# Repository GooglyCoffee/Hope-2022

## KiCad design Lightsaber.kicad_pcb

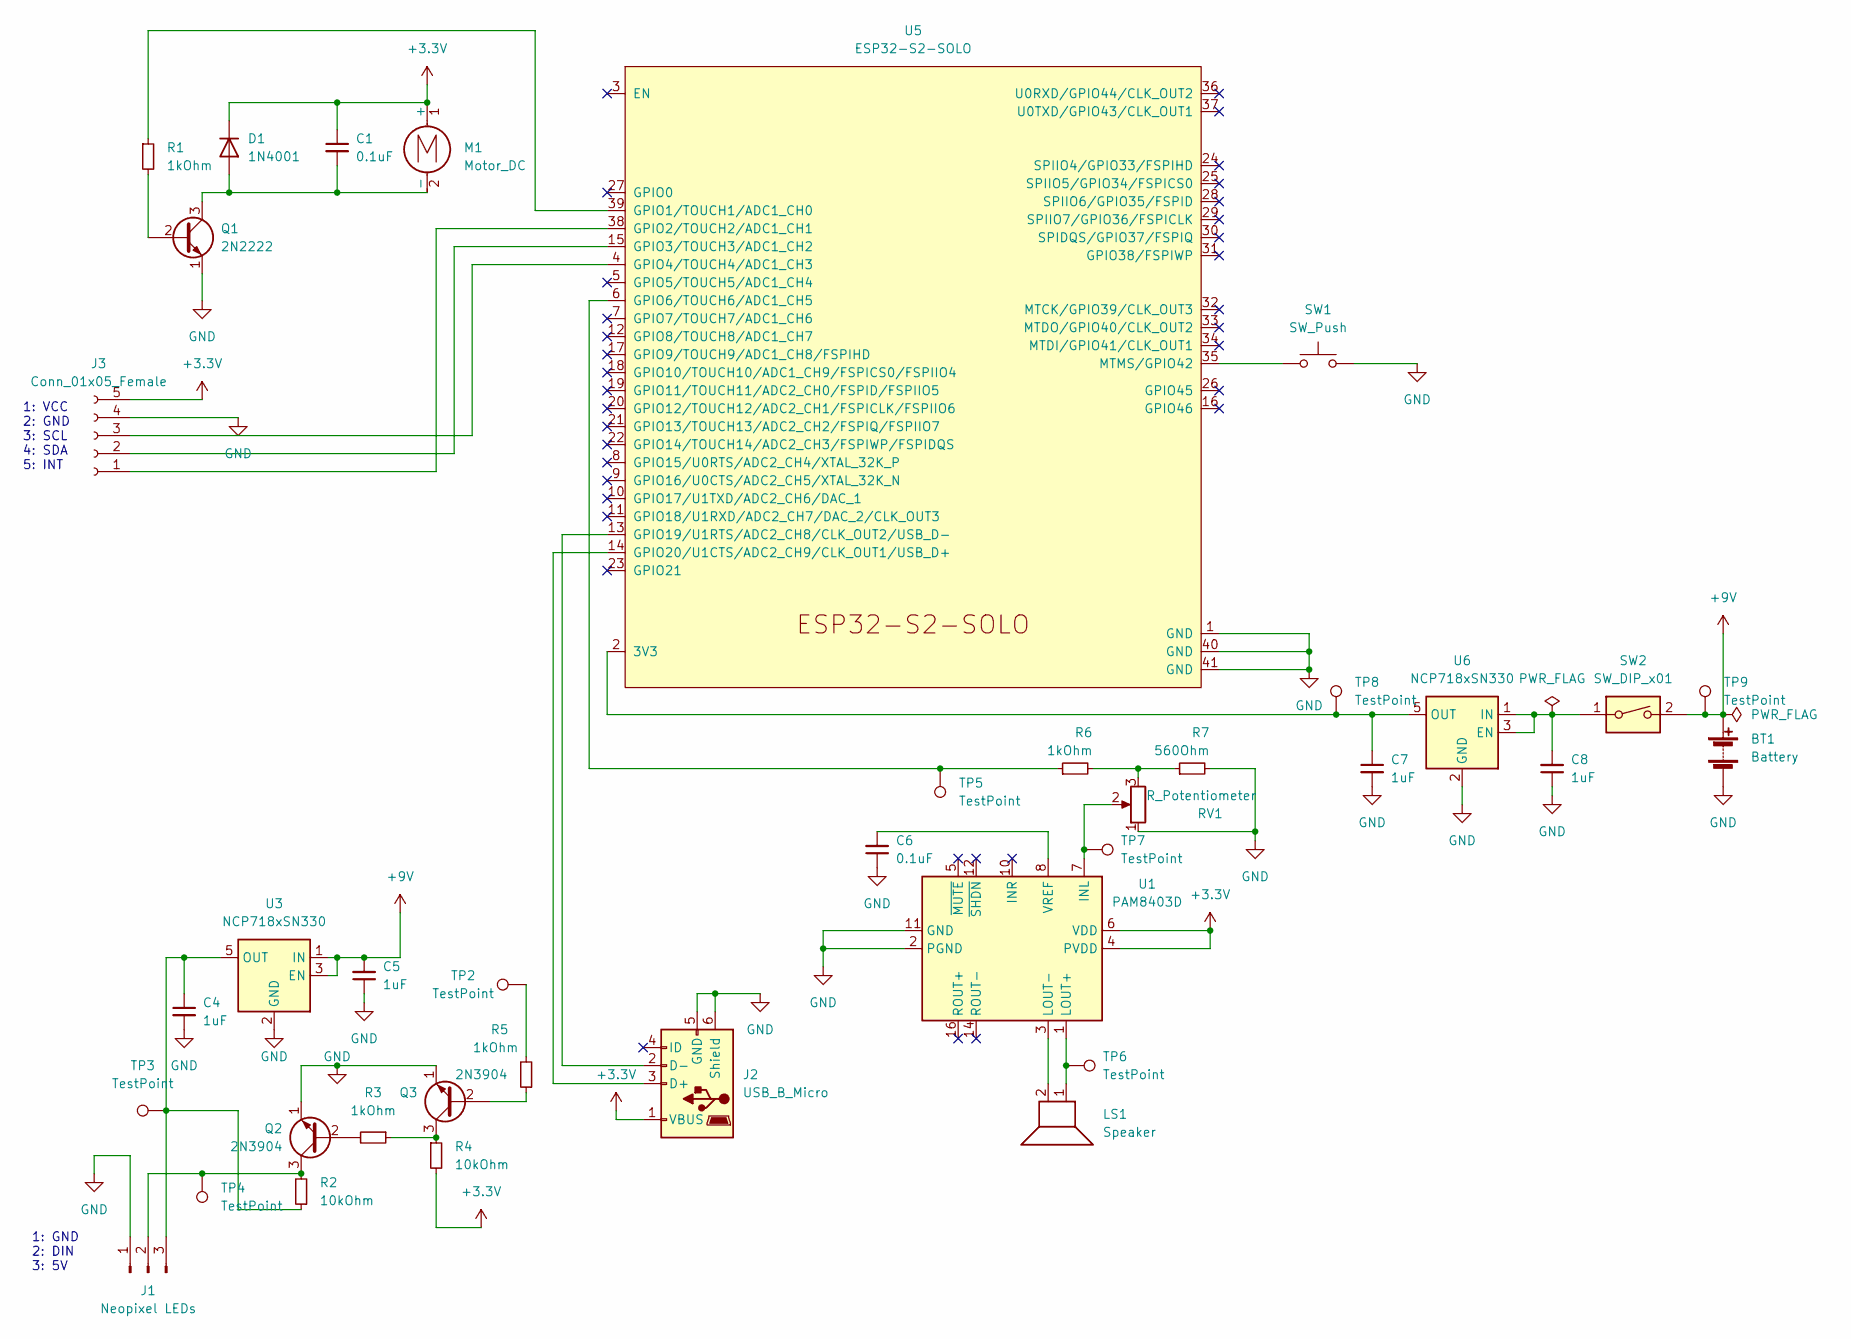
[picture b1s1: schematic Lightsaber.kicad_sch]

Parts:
BT1: Battery
C1, C6: 0.1uF; C_0201_0603Metric
C4, C5, C7, C8: 1uF; C_0603_1608Metric
D1: 1N4001; D_SOD-123F
J1: Neopixel LEDs; LED strip
J2: USB_B_Micro; USB_Micro-B_Molex-105017-0001
J3: Conn_01x05_Female; PinSocket_1x05_P2.54mm_Vertical
LS1: Speaker
M1: Motor_DC; Motor
Q1: 2N2222; TO-39-3
Q2, Q3: 2N3904; TO-92_Inline
R1, R3, R5, R6: 1kOhm; R_0603_1608Metric
R2, R4: 10kOhm; R_0603_1608Metric
R7: 560Ohm; R_0603_1608Metric
RV1: R_Potentiometer; Potentiometer
SW1: SW_Push; Switch
SW2: SW_DIP_x01; Switch toggle
TP2, TP3, TP4, TP5, TP6, TP7, TP8, TP9: TestPoint; PinHeader_1x01_P1.00mm_Vertical
U1: PAM8403D; SOP-16_3.9x9.9mm_P1.27mm
U3, U6: NCP718xSN330; SOT-23-5
U5: ESP32-S2-SOLO

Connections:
+3.3V: C1.1, D1.1 (K), J2.1 (VBUS), J3.5, M1.1 (+), R4.2, U1.4 (PVDD), U1.6 (VDD), U1.13 (PVDD)
+9V: BT1.1 (+), C5.2, SW2.2, TP9.1, U3.1 (IN), U3.3 (EN)
GND: BT1.2 (-), C4.2, C5.1, C6.1, C7.2, C8.1, J1.1, J2.5 (GND), J2.6 (Shield), J3.4, Q1.1 (E), Q2.1 (E), Q3.1 (E), R7.2, RV1.1, SW1.2, U1.2 (PGND), U1.11 (GND), U1.15 (PGND), U3.2 (GND), U5.1 (GND), U5.40 (GND), U5.41 (GND), U6.2 (GND)
unnamed: C1.2, D1.2 (A), M1.2 (-), Q1.3 (C)
unnamed: C4.1, J1.3, R2.1, TP3.1, U3.5 (OUT)
unnamed: C6.2, U1.8 (VREF)
unnamed: C7.1, TP8.1, U5.2 (3V3), U6.5 (OUT)
unnamed: C8.2, SW2.1, U6.1 (IN), U6.3 (EN)
unnamed: J1.2, Q2.3 (C), R2.2, TP4.1
unnamed: J2.2 (D-), U5.13 (GPIO19/U1RTS/ADC2_CH8/CLK_OUT2/USB_D-)
unnamed: J2.3 (D+), U5.14 (GPIO20/U1CTS/ADC2_CH9/CLK_OUT1/USB_D+)
unnamed: LS1.1, TP6.1, U1.1 (LOUT+)
unnamed: LS1.2, U1.3 (LOUT-)
unnamed: Q1.2 (B), R1.2
unnamed: Q2.2 (B), R3.2
unnamed: Q3.2 (B), R5.1
unnamed: Q3.3 (C), R3.1, R4.1
unnamed: R1.1, U5.39 (GPIO1/TOUCH1/ADC1_CH0)
unnamed: R5.2, TP2.1
unnamed: R6.1, TP5.1, U5.6 (GPIO6/TOUCH6/ADC1_CH5)
unnamed: R6.2, R7.1, RV1.3
unnamed: RV1.2, TP7.1, U1.7 (INL)
unnamed: SW1.1, U5.35 (MTMS/GPIO42)
unnamed: J3.3, U5.4 (GPIO4/TOUCH4/ADC1_CH3)
unnamed: J3.2, U5.15 (GPIO3/TOUCH3/ADC1_CH2)
unnamed: J3.1, U5.38 (GPIO2/TOUCH2/ADC1_CH1)

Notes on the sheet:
1: GND 2: DIN 3: 5V
1: VCC 2: GND 3: SCL 4: SDA 5: INT

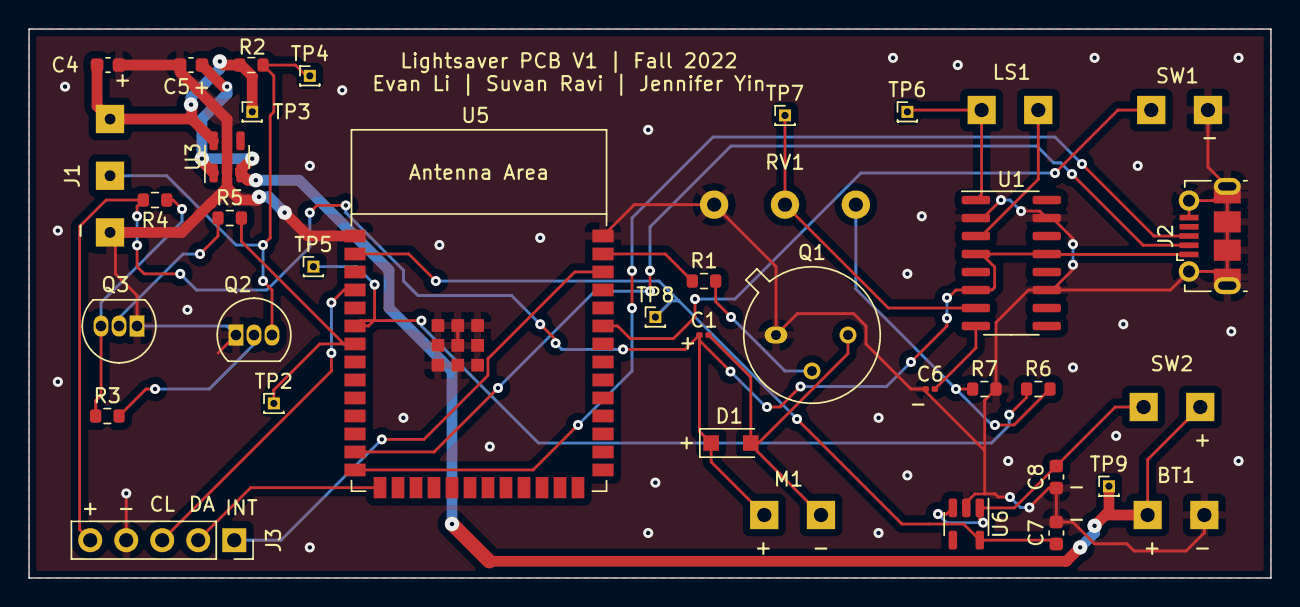
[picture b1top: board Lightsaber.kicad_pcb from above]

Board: 2 copper layers, 87.6 x 38.7 mm, 38 parts (0 on the bottom side), 26 nets.

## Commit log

2022-11-11 added test points and footprints
2022-11-11 thickened power traces, fixed all errors, placed test points on layout
2022-11-11 finished
